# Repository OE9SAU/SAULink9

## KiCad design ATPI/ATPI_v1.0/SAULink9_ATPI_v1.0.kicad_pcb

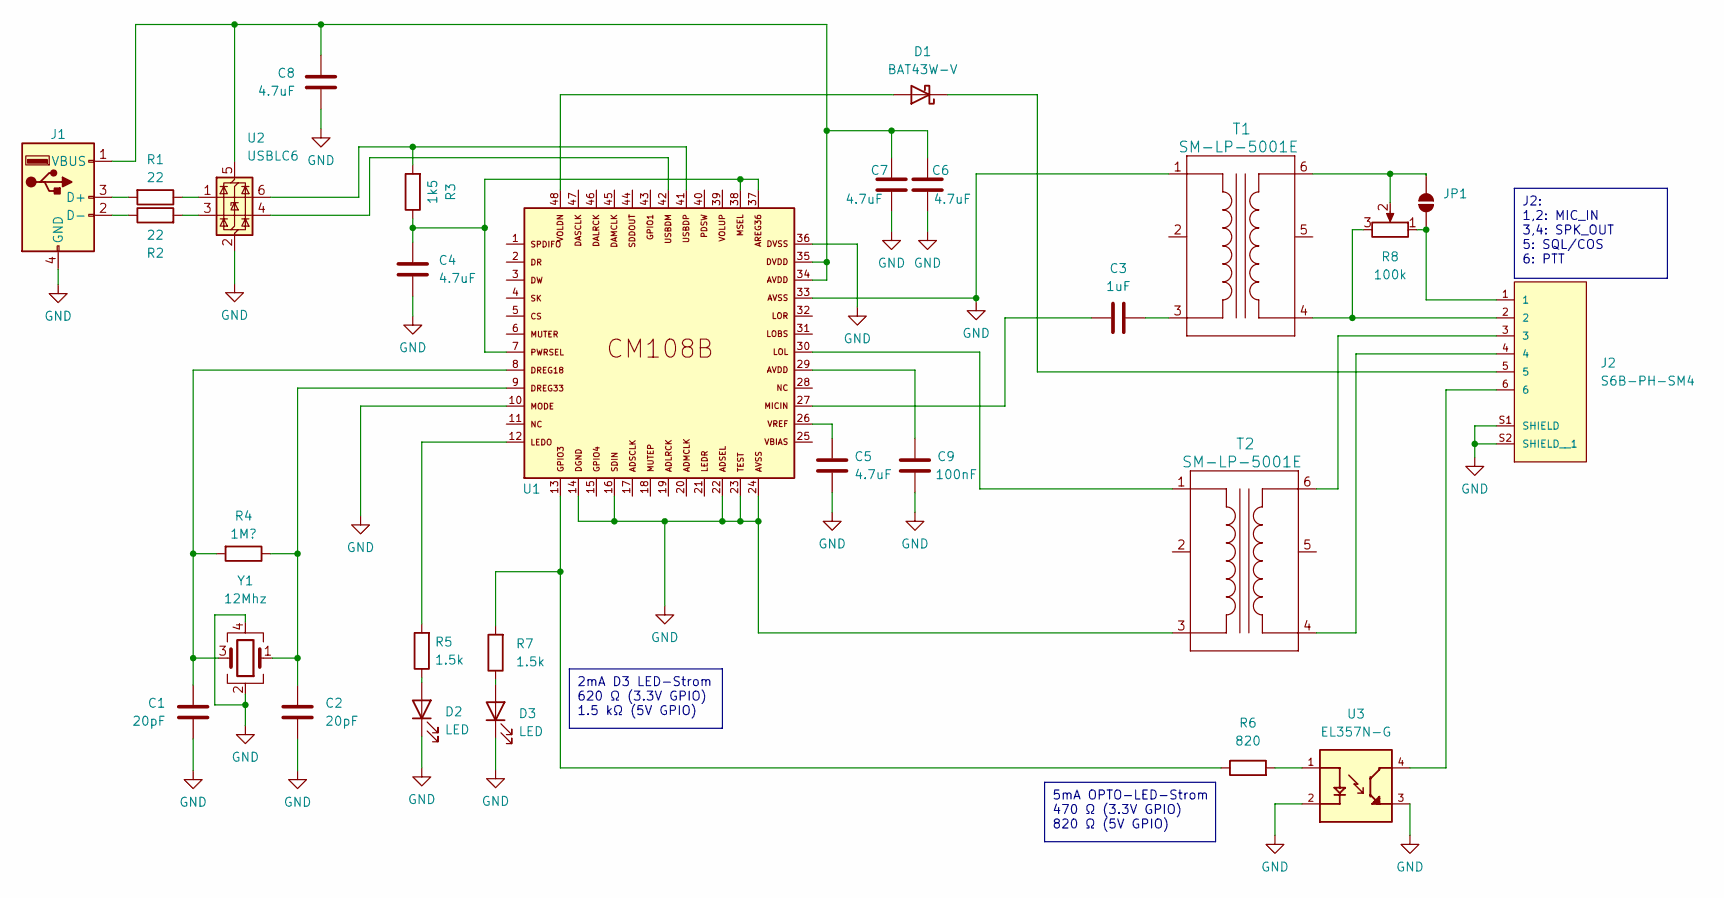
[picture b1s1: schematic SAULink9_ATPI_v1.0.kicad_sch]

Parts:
C1, C2: 20pF; C_0805_2012Metric_Pad1.18x1.45mm_HandSolder
C3: 1uF; C_0805_2012Metric
C4, C5, C6, C7, C8: 4.7uF; C_0805_2012Metric
C9: 100nF; C_0805_2012Metric
D1: BAT43W-V; D_SOD-323
D2, D3: LED; LED_0805_2012Metric
J1: USB_A_PCB_Edge_receptacle
J2: S6B-PH-SM4; JST_S6B-PH-SM4-TB_LF__SN_
JP1: SolderJumper_2_Open; SolderJumper-2_P1.3mm_Open_RoundedPad1.0x1.5mm
R1, R2: 22; R_0805_2012Metric
R3: 1k5; R_0805_2012Metric
R4: 1M?; R_0805_2012Metric
R5, R7: 1.5k; R_0805_2012Metric
R6: 820; R_0805_2012Metric
R8: 100k; Potentiometer_Bourns_TC33X_Vertical
T1, T2: SM-LP-5001E; RES6_SM-LP-5001E_BRN
U1: CM108B; TQFP48
U2: USBLC6; SOT-23-6
U3: EL357N-G; OPTO_EL357N-G; PARTREV 6
Y1: 12Mhz; Crystal_SMD_3225-4Pin_3.2x2.5mm

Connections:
GND: C1.1, C2.2, C4.2, C5.2, C6.2, C7.2, C8.2, C9.2, D2.1 (K), D3.1 (K), J1.4 (GND), J2.S1 (SHIELD), J2.S2 (SHIELD__1), T1.1, T2.3, U1.10, U1.14, U1.16, U1.22, U1.23, U1.24, U1.33, U1.36, U2.2 (GND), U3.2, U3.3, Y1.2, Y1.4
unnamed: C1.2, R4.2, U1.8, Y1.3
unnamed: C2.1, R4.1, U1.9, Y1.1
unnamed: C3.1, U1.27
unnamed: C3.2, T1.3
unnamed: C4.1, R3.1, U1.7, U1.37, U1.38
unnamed: C5.1, U1.26
unnamed: C9.1, U1.29
unnamed: D1.2 (A), U1.48
unnamed: D1.1 (K), J2.5
unnamed: D2.2 (A), R5.1
unnamed: D3.2 (A), R7.1
unnamed: J1.3 (D+), R1.2
unnamed: J1.2 (D-), R2.1
unnamed: C6.1, C7.1, C8.1, J1.1 (VBUS), U1.34, U1.35, U2.5 (VBUS)
unnamed: J2.2, R8.3, T1.4
unnamed: J2.3, T2.6
unnamed: J2.4, T2.4
unnamed: J2.6, U3.4
unnamed: J2.1, JP1.1 (A), R8.1
unnamed: JP1.2 (B), R8.2, T1.6
unnamed: R1.1, U2.1 (I/O1)
unnamed: R2.2, U2.3 (I/O2)
unnamed: R3.2, U1.41, U2.6 (I/O1)
unnamed: R5.2, U1.12
unnamed: R6.1, R7.2, U1.13
unnamed: R6.2, U3.1
unnamed: T2.1, U1.30
unnamed: U1.42, U2.4 (I/O2)

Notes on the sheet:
2mA D3 LED-Strom 620 Ω (3.3V GPIO) 1.5 kΩ (5V GPIO)
5mA OPTO-LED-Strom 470 Ω (3.3V GPIO) 820 Ω (5V GPIO)
J2: 1,2: MIC_IN 3,4: SPK_OUT 5: SQL/COS 6: PTT

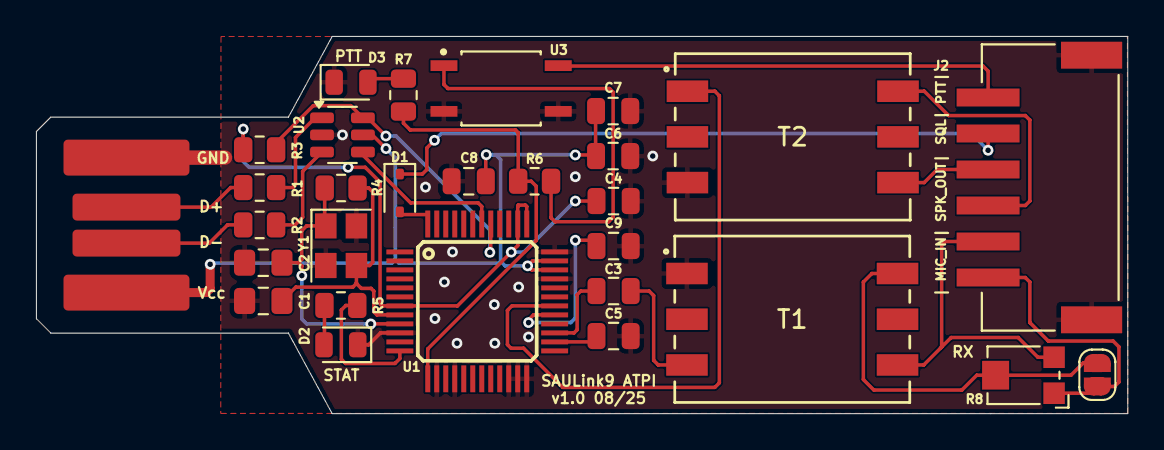
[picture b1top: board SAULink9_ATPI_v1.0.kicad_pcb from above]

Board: 2 copper layers, 60.6 x 21.0 mm, 30 parts (1 on the bottom side), 29 nets.

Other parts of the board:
g2: LOGO
